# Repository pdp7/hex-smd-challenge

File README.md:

# hex-smd-challenge
SMD Challenge by Maker's Box (Ken Olsen) in hex sticker format for OSH Park

- [Shared project](https://oshpark.com/shared_projects/DrxdADP3)
- [Tindie](https://www.tindie.com/products/MakersBox/smd-challenge/)

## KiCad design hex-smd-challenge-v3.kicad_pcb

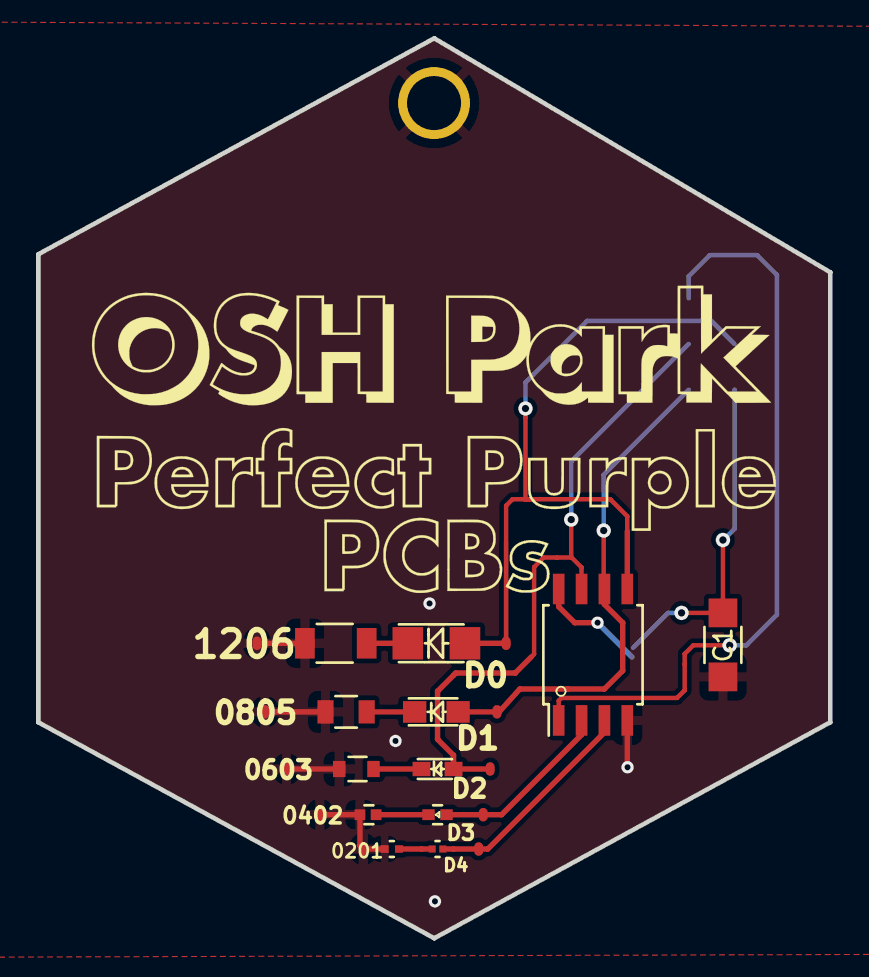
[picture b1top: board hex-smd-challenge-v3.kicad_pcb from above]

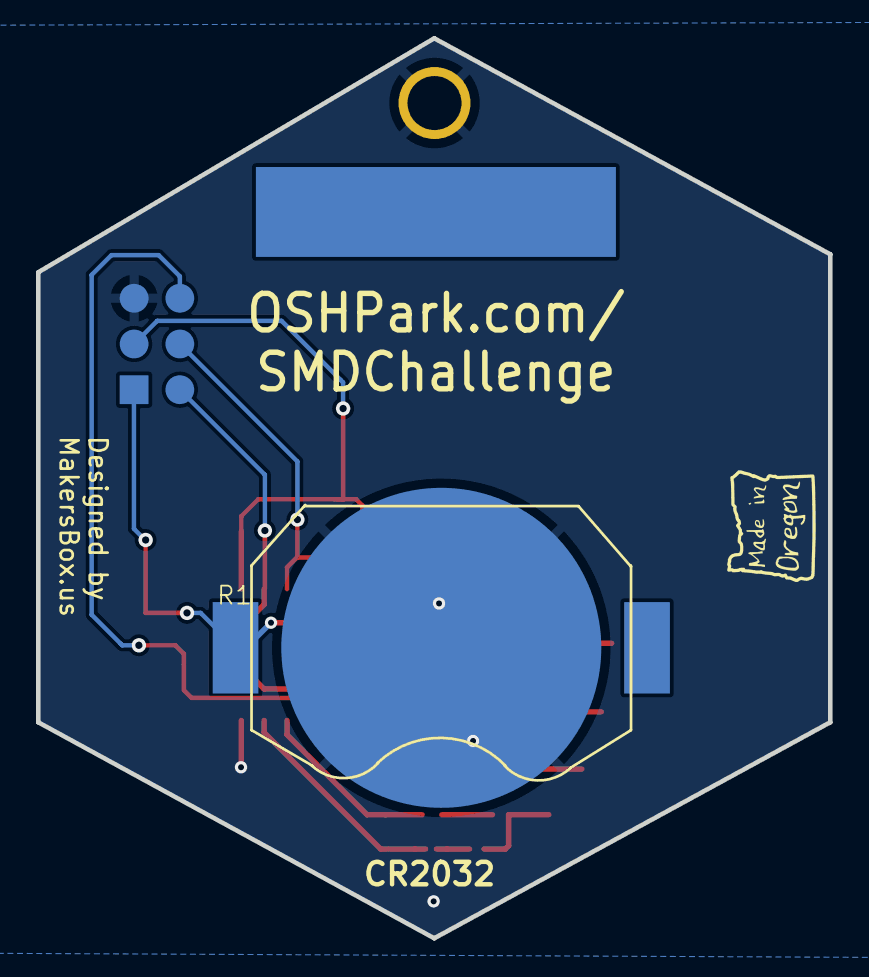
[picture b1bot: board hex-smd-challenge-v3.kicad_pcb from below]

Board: 2 copper layers, 44.0 x 50.0 mm, 28 parts (2 on the bottom side), 13 nets.

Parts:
BT1: Battery; BATT_CR2032_SMD
C1: 0.1 uF; C_1206_HandSoldering
CON1: AVR-ISP-6
D0: LED; LED-1206
D1: LED; LED-0805
D2: LED; LED-0603
D3: LED; LED_0402
D4: LED; LED_0201
IC1: IC1; SOIJ-8_5.3x5.3mm_Pitch1.27mm
P0, P1#2, P2, P3, P4: CONN_01X01; testPad
P1: CONN_01X01; Pin_Header_Straight_1x01
PG0, PG1, PG2, PG3, PG4: CONN_01X01; testPad
R0: 330; R_1206
R1: 330; R_0805
R2: 330; R_0603
R3: 330; R_0402
R4: 330; R_0201
Ref**: Val**; oshpark-v2-ppp
Ref**#2: Val**; oshpark-v2-oshpark
VAL: MadeInOregonRev25

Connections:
+BATT: BT1.1, C1.2, CON1.2, IC1.8
GND: BT1.2, C1.1, CON1.6, IC1.4, PG0.1, PG1.1, PG2.1, PG3.1, PG4.1, R0.2, R1.2, R2.2, R3.2, R4.2
unnamed: CON1.1, D1.2, IC1.6, P1#2.1
unnamed: CON1.3, D2.2, IC1.7, P2.1
unnamed: CON1.4, D0.2, IC1.5, P0.1
unnamed: CON1.5, IC1.1
unnamed: D0.1, R0.1
unnamed: D1.1, R1.1
unnamed: D2.1, R2.1
unnamed: D3.1, R3.1
unnamed: D3.2, IC1.2, P3.1
unnamed: D4.1, R4.1
unnamed: D4.2, IC1.3, P4.1

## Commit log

2020-12-05 update ignore file
2020-12-05 add initial version of files
    this project started from Attiny85Challenge2 in github.com/aspro648/KiCad
    which is the SMD Challenge by Maker's Box (Ken Olsen)
2020-12-06 Fixed C1. TODO: ISP header is missing
2020-12-18 add new version of design including v2 which went to fab
2020-12-19 update logo based on svg
2020-12-19 improve oshpark text
2021-01-03 add missing silk
2021-01-05 add v4
